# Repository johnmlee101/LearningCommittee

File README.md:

# LearningCommittee
This repository is the home for all of Purdue IEEE Learning committee files and folders that are shared for its members. 
##Setup
For all new members, please install git on your computer. Easiest way is to install *GitHub Desktop* at https://desktop.github.com/.

Once installed, please add this repository by starring it on the top right on this page, then click the 'Save to computer' button to the left of **Download ZIP**.
Once downloaded, you can now access all of the files and keep up to date by syncing using the desktop application.

To learn git, try this handy website! (For terminal Git)
https://try.github.io/levels/1/challenges/1

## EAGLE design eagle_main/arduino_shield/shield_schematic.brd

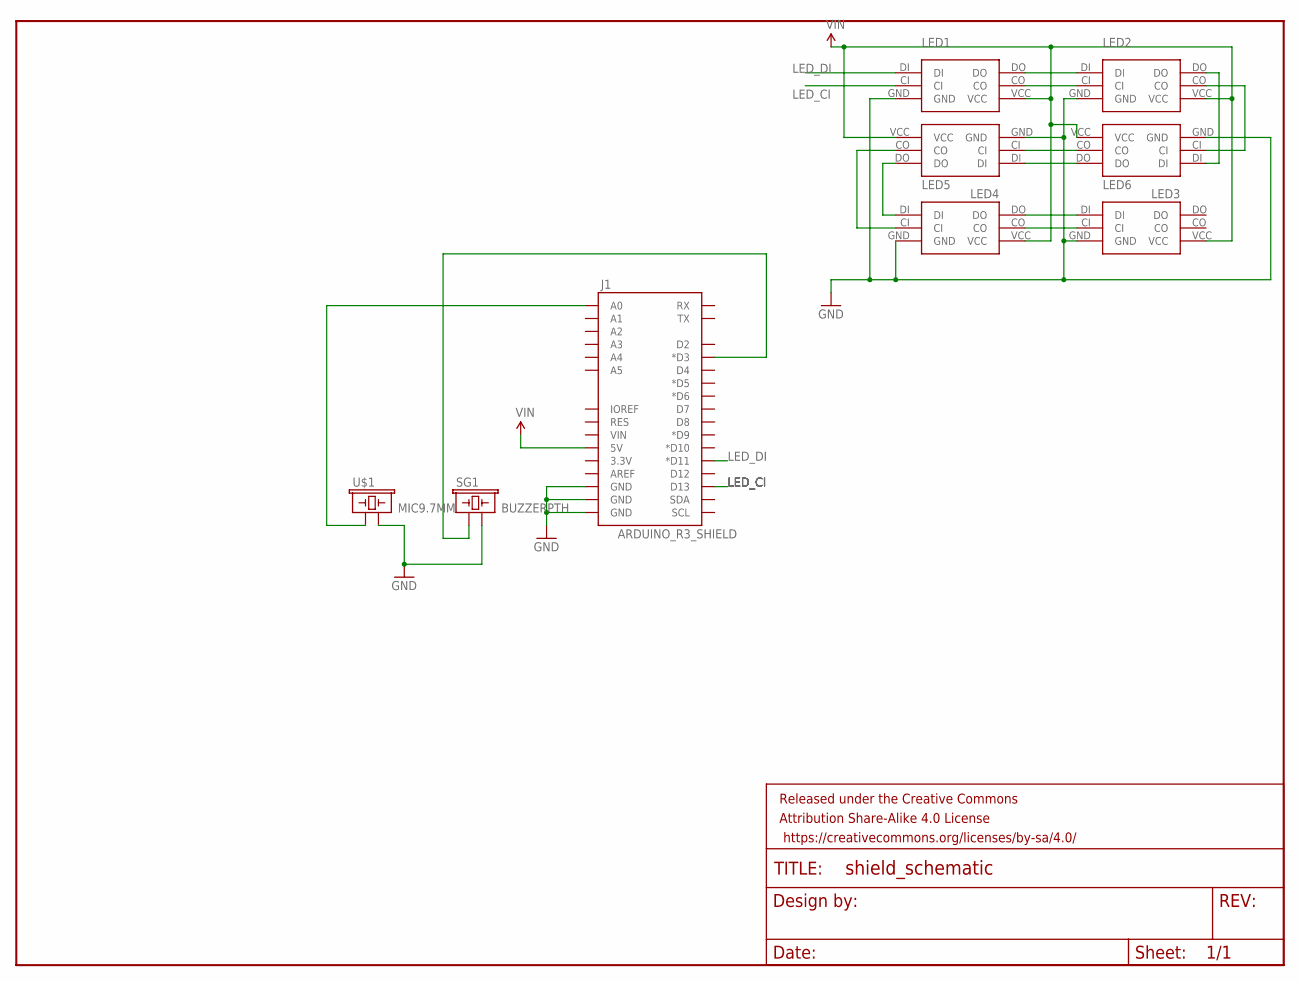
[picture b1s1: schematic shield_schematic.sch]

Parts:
FRAME1: FRAME-LETTER; CREATIVE_COMMONS
J1: ARDUINO_R3_SHIELD; UNO_R3_SHIELD
LED1, LED2, LED3, LED4, LED5, LED6: APA102SMD; RGBLED5050
SG1: BUZZERPTH; BUZZER-12MM
U$1: MIC9.7MM; MIC-9.7MM

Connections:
GND: J1.GND@0 (GND), J1.GND@1 (GND), J1.GND@2 (GND), LED1.GND, LED2.GND, LED3.GND, LED4.GND, LED5.GND, LED6.GND, SG1.- (2), U$1.2
LED_CI: J1.D13, LED1.CI
LED_DI: J1.D11 (*D11), LED1.DI
unnamed: J1.A0, U$1.1
unnamed: J1.D3 (*D3), SG1.+ (1)
unnamed: LED1.DO, LED2.DI
unnamed: LED1.CO, LED2.CI
unnamed: LED2.DO, LED3.DI
unnamed: LED2.CO, LED3.CI
unnamed: LED3.CO, LED4.CI
unnamed: LED3.DO, LED4.DI
unnamed: LED4.CO, LED5.CI
unnamed: LED4.DO, LED5.DI
unnamed: LED5.DO, LED6.DI
unnamed: LED5.CO, LED6.CI
VIN: J1.5V, LED1.VCC, LED2.VCC, LED3.VCC, LED4.VCC, LED5.VCC, LED6.VCC

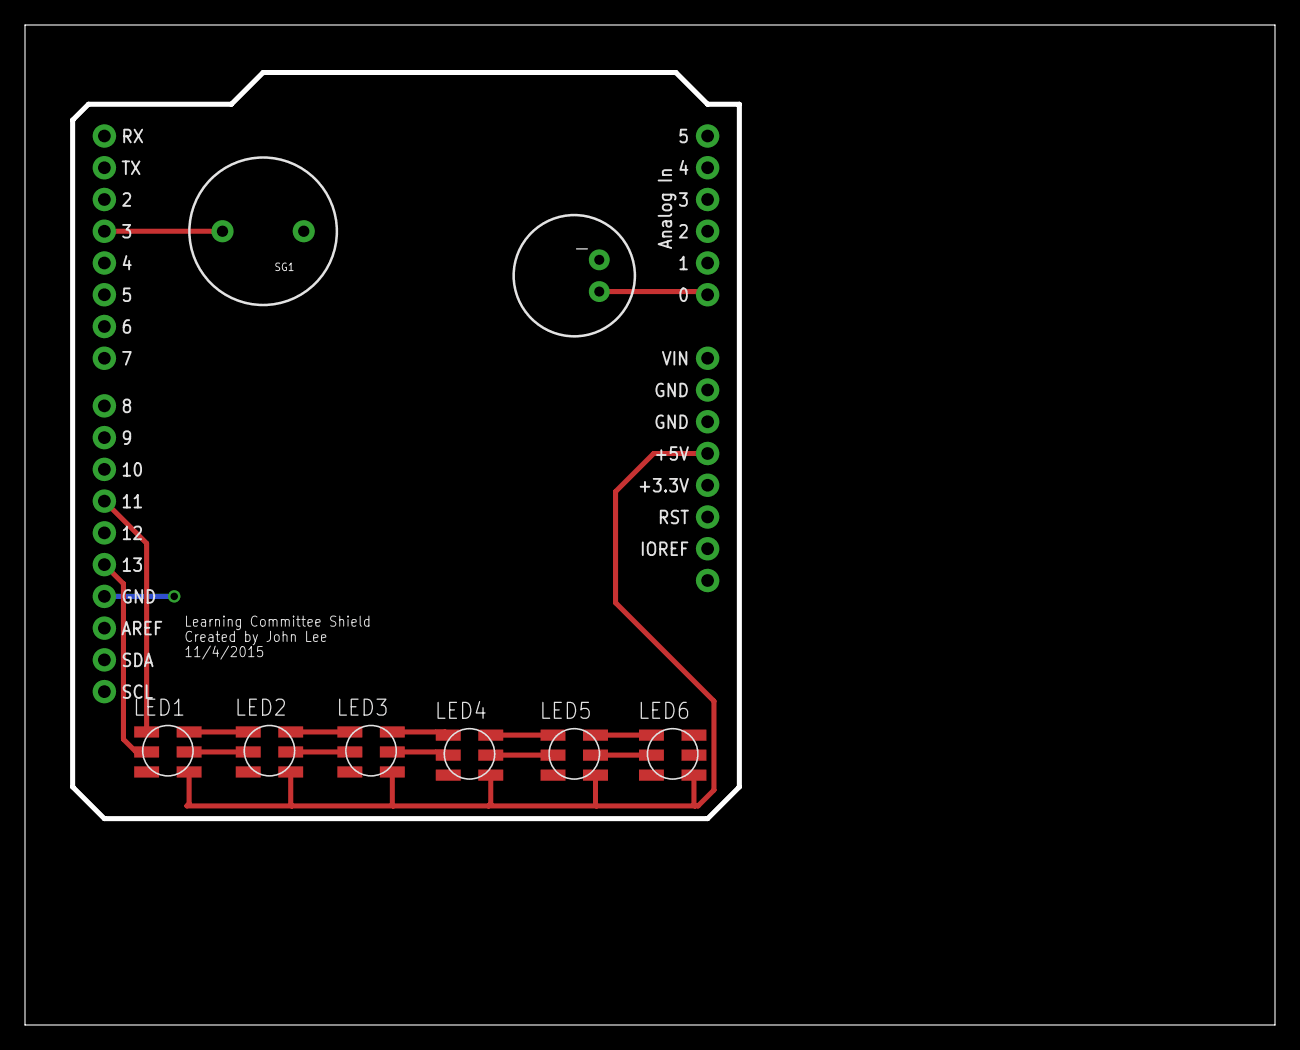
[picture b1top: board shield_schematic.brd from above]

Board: 2 copper layers, 100.0 x 80.0 mm, 10 parts (0 on the bottom side), 16 nets.

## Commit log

2015-10-29 Added PCB Parts for RGB LED
2015-10-29 Removed meta-email-thingy
2015-10-29 Added Eagle files
2015-10-29 Added random file for testing
2015-10-29 Reverted test
2015-11-04 Updated parts for November 4th
2015-11-04 added git ignore
2015-11-04 Removed unnecessary files
2015-11-04 Added LED Part
2016-01-25 Created README

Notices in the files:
parts and their libraries:
SparkFun-Aesthetics: Licensing: Creative Commons ShareAlike 4.0 International - https://creativecommons.org/licenses/by-sa/4.0
SparkFun-Aesthetics: Released under the Creative Commons Attribution Share-Alike 4.0 License
SparkFun-Aesthetics: https://creativecommons.org/licenses/by-sa/4.0
